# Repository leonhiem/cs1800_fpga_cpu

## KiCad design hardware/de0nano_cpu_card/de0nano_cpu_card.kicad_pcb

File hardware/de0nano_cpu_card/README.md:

# CS1800 DE0-Nano CPU Card (KiCad project)

Eurocard CPU board that plugs a Terasic DE0-Nano (running a VHDL CDP1802 core) into the
existing CS1800 backplane, replacing the original 1802 CPU board.

## Opening this project

Use **KiCad 10.0.6** (`~/bin/kicad-10.0.6-x86_64.AppImage`), not the older KiCad 6 install
that's on `PATH` — this project's files are in KiCad 10's native format and KiCad 6 will
not open them.

```
~/bin/kicad-10.0.6-x86_64.AppImage hardware/de0nano_cpu_card/de0nano_cpu_card.kicad_pro
```

Headless checks (ERC/DRC/export) can be run without launching the GUI via the wrapper
script `~/bin/kicad-cli10` (FUSE-mounts the AppImage's `kicad-cli` on demand, no full
extraction needed):

```
~/bin/kicad-cli10 sch erc de0nano_cpu_card.kicad_sch
~/bin/kicad-cli10 pcb drc de0nano_cpu_card.kicad_pcb
```

## Status (2026-10-09)

Architecture, mechanical/sourcing, and FPGA pin assignment are all resolved. All 7
schematic sheets are wired with real nets (`kicad-cli sch erc`: 0 errors) — see
`docs/design_notes.md` for the full writeup, the JLCPCB-oriented component shortlist,
and the "Next steps" list (custom footprints, PCB floorplan/routing are what's left).
The sheets were generated via the scripts in `tools/` (see `tools/README.md`) from the
pin data in `docs/cs1800.qsf` and the other `docs/` files — re-run the relevant
`tools/build_*.py` after a pinout change rather than hand-editing the `.kicad_sch` output.

## Layout

```
de0nano_cpu_card.kicad_pro/.kicad_sch/.kicad_pcb   top-level project + root (hierarchical) schematic + PCB
sheets/                                             one schematic per functional block
libraries/symbols/cs1800.kicad_sym                  project-local custom symbols
libraries/footprints/cs1800.pretty/                 project-local custom footprints
docs/                                                design notes, pinout docs, FPGA .qsf, connector datasheet
tools/                                               schematic generator scripts (see tools/README.md)
jlcpcb/                                              (empty for now) gerbers/BOM/CPL export target once ready
```

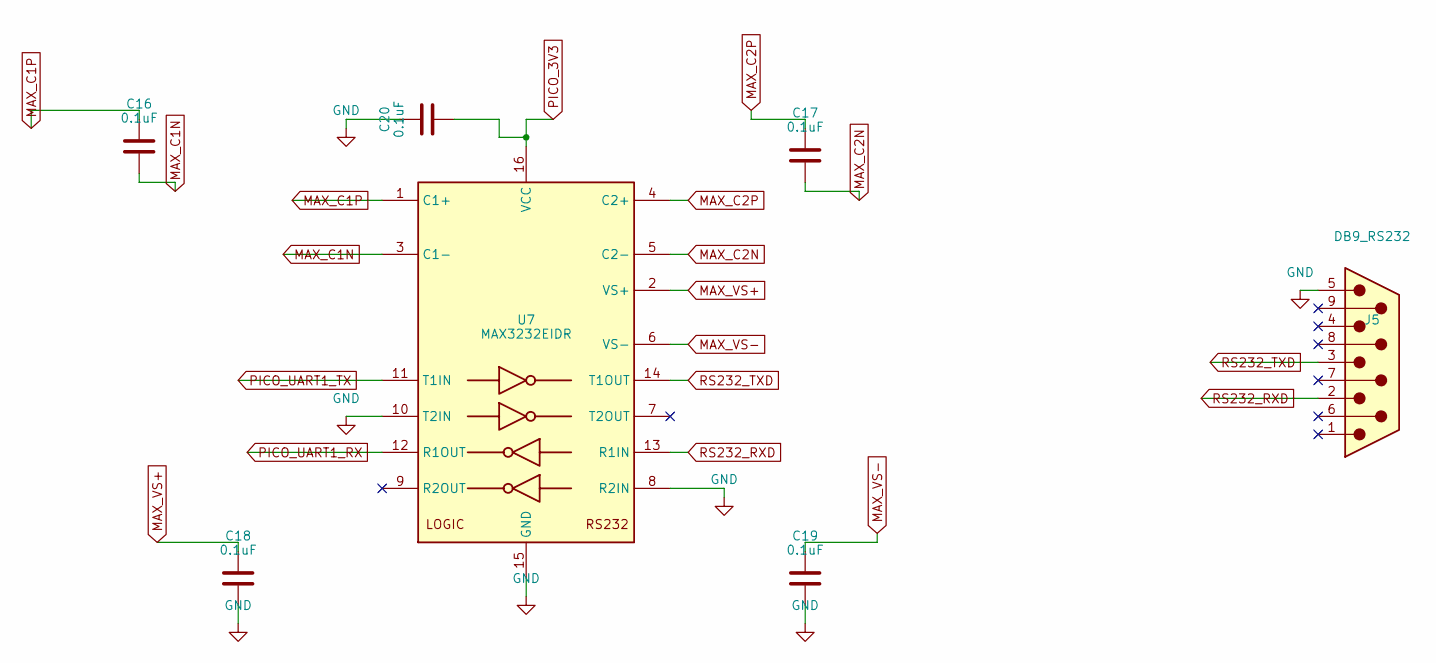
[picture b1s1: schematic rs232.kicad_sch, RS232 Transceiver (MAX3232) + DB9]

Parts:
C16, C17, C18, C19, C20: 0.1uF; C_0603_1608Metric
J5: DB9_RS232; DSUB-9_Pins_Horizontal_P2.77x2.54mm_EdgePinOffset9.40mm
U7: MAX3232EIDR; SOIC-16_3.9x9.9mm_P1.27mm

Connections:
GND: C18.2, C19.2, C20.1, J5.5, U7.8 (R2IN), U7.10 (T2IN), U7.15 (GND); also elsewhere on the board
MAX_C1N: C16.2, U7.3 (C1-)
MAX_C1P: C16.1, U7.1 (C1+)
MAX_C2N: C17.2, U7.5 (C2-)
MAX_C2P: C17.1, U7.4 (C2+)
MAX_VS+: C18.1, U7.2 (VS+)
MAX_VS-: C19.1, U7.6 (VS-)
PICO_3V3: C20.2, U7.16 (VCC); also elsewhere on the board
PICO_UART1_RX: U7.12 (R1OUT); also elsewhere on the board
PICO_UART1_TX: U7.11 (T1IN); also elsewhere on the board
RS232_RXD: J5.2, U7.13 (R1IN)
RS232_TXD: J5.3, U7.14 (T1OUT)

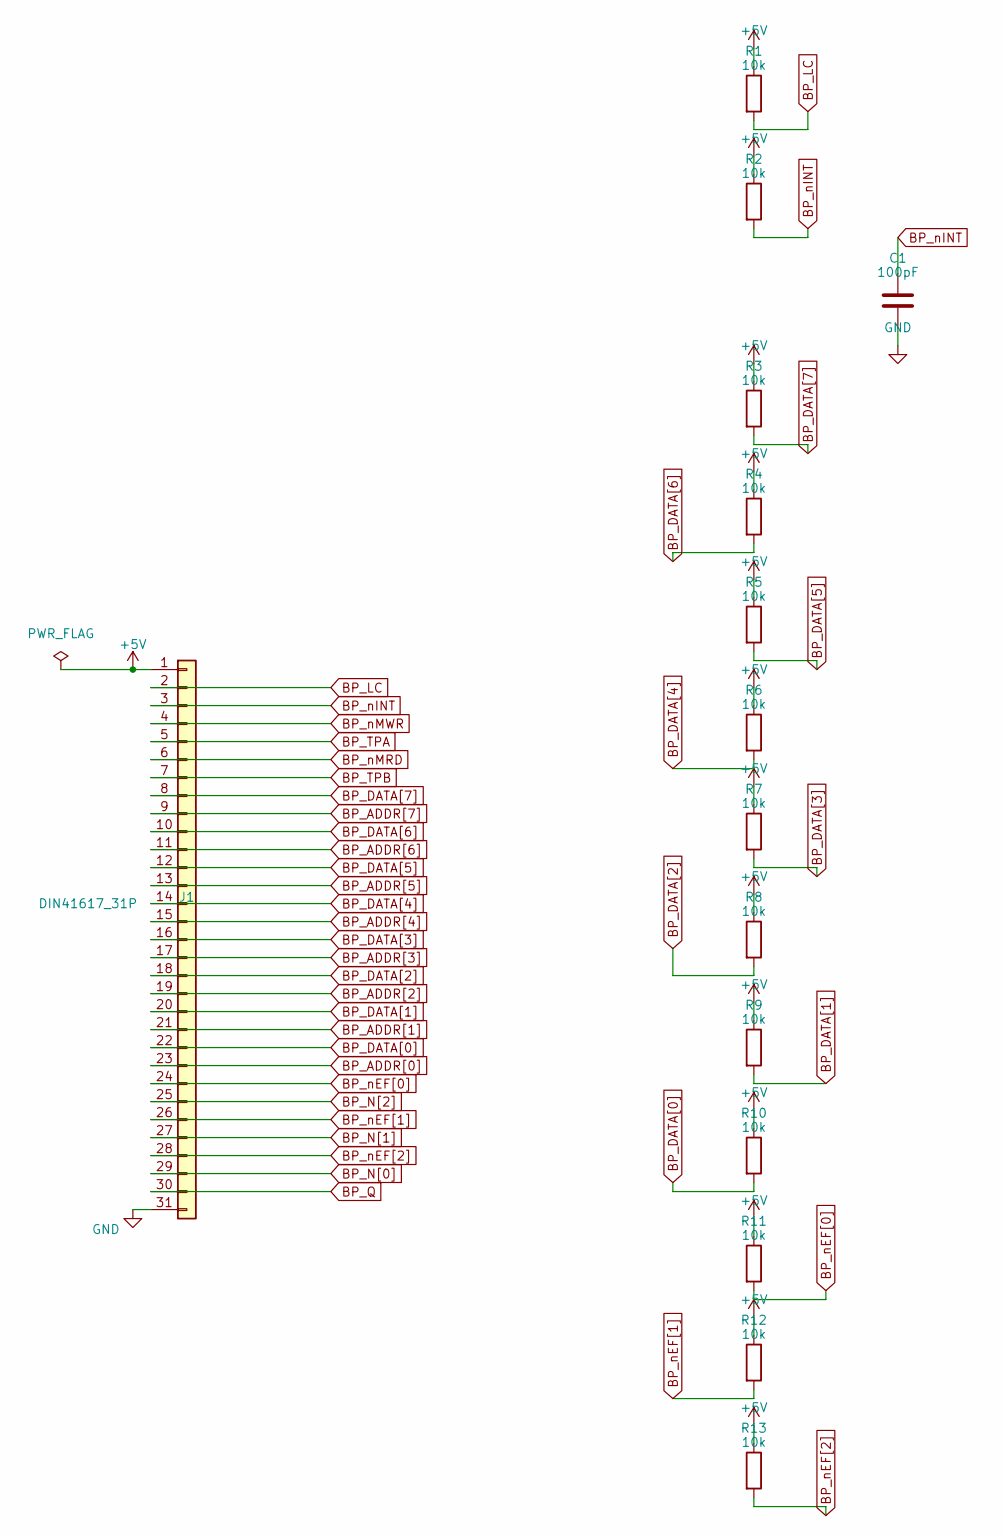
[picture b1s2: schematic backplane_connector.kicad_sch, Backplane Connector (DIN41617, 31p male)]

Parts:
C1: 100pF; C_0603_1608Metric
J1: DIN41617_31P; DIN41617_31P_Male_Angled
R1, R2, R3, R4, R5, R6, R7, R8, R9, R10, R11, R12, R13: 10k; R_0603_1608Metric

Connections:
+5V: J1.1, R1.1, R2.1, R3.1, R4.1, R5.1, R6.1, R7.1, R8.1, R9.1, R10.1, R11.1, R12.1, R13.1; also elsewhere on the board
BP_ADDR[0]: J1.23; also elsewhere on the board
BP_ADDR[1]: J1.21; also elsewhere on the board
BP_ADDR[2]: J1.19; also elsewhere on the board
BP_ADDR[3]: J1.17; also elsewhere on the board
BP_ADDR[4]: J1.15; also elsewhere on the board
BP_ADDR[5]: J1.13; also elsewhere on the board
BP_ADDR[6]: J1.11; also elsewhere on the board
BP_ADDR[7]: J1.9; also elsewhere on the board
BP_DATA[0]: J1.22, R10.2; also elsewhere on the board
BP_DATA[1]: J1.20, R9.2; also elsewhere on the board
BP_DATA[2]: J1.18, R8.2; also elsewhere on the board
BP_DATA[3]: J1.16, R7.2; also elsewhere on the board
BP_DATA[4]: J1.14, R6.2; also elsewhere on the board
BP_DATA[5]: J1.12, R5.2; also elsewhere on the board
BP_DATA[6]: J1.10, R4.2; also elsewhere on the board
BP_DATA[7]: J1.8, R3.2; also elsewhere on the board
BP_LC: J1.2, R1.2; also elsewhere on the board
BP_N[0]: J1.29; also elsewhere on the board
BP_N[1]: J1.27; also elsewhere on the board
BP_N[2]: J1.25; also elsewhere on the board
BP_Q: J1.30; also elsewhere on the board
BP_TPA: J1.5; also elsewhere on the board
BP_TPB: J1.7; also elsewhere on the board
BP_nEF[0]: J1.24, R11.2; also elsewhere on the board
BP_nEF[1]: J1.26, R12.2; also elsewhere on the board
BP_nEF[2]: J1.28, R13.2; also elsewhere on the board
BP_nINT: C1.1, J1.3, R2.2; also elsewhere on the board
BP_nMRD: J1.6; also elsewhere on the board
BP_nMWR: J1.4; also elsewhere on the board
GND: C1.2, J1.31; also elsewhere on the board

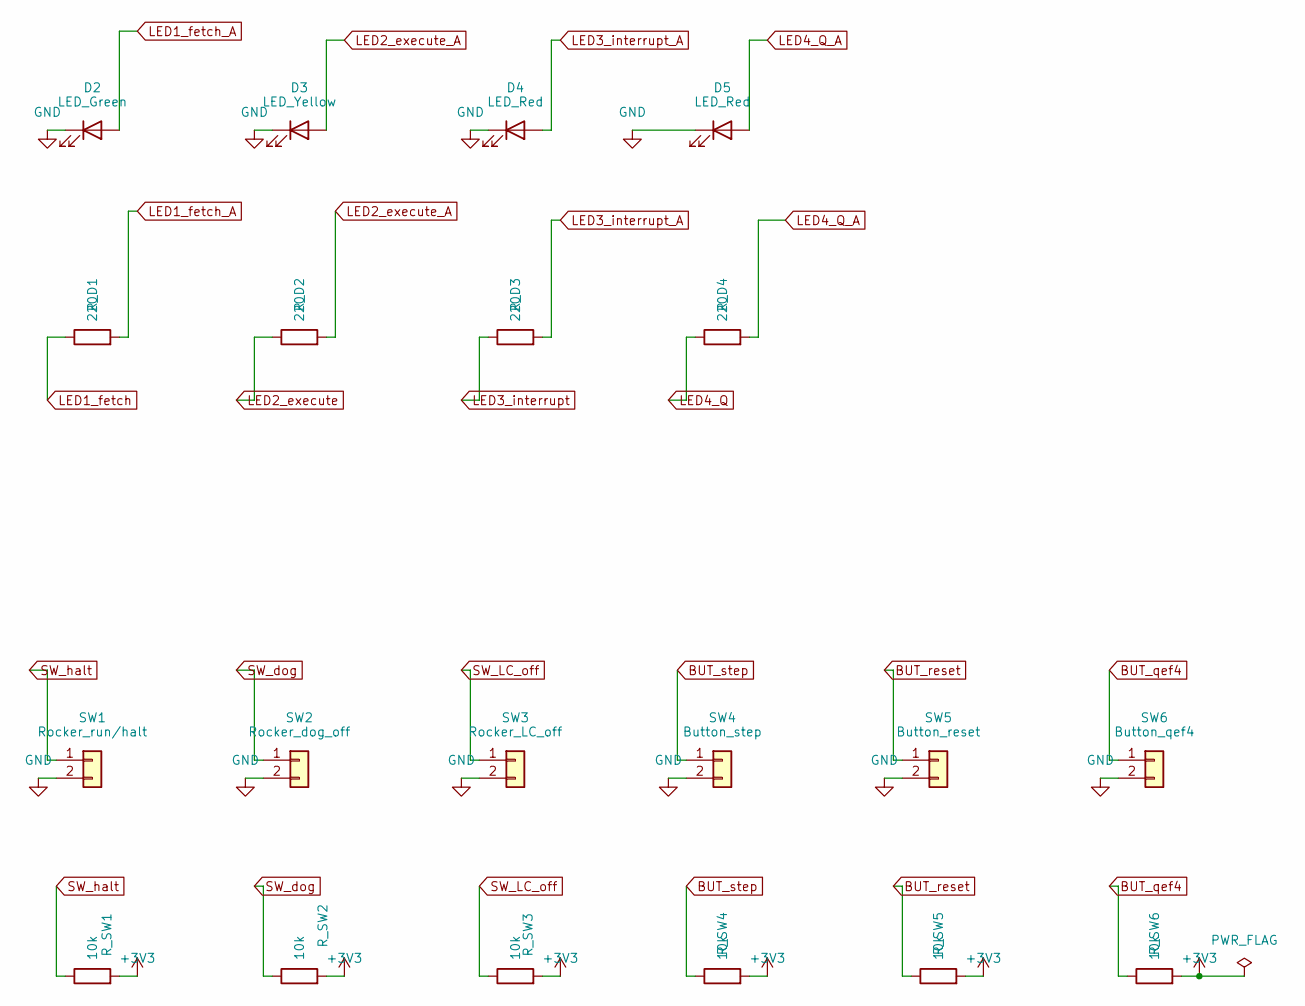
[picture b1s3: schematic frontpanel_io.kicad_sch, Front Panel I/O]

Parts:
D2: LED_Green; LED_D3.0mm
D3: LED_Yellow; LED_D3.0mm
D4, D5: LED_Red; LED_D3.0mm
R_D1, R_D2, R_D3, R_D4: 220; R_0603_1608Metric
R_SW1, R_SW2, R_SW3, R_SW4, R_SW5, R_SW6: 10k; R_0603_1608Metric
SW1: Rocker_run/halt; PinHeader_1x02_P2.54mm_Vertical
SW2: Rocker_dog_off; PinHeader_1x02_P2.54mm_Vertical
SW3: Rocker_LC_off; PinHeader_1x02_P2.54mm_Vertical
SW4: Button_step; PinHeader_1x02_P2.54mm_Vertical
SW5: Button_reset; PinHeader_1x02_P2.54mm_Vertical
SW6: Button_qef4; PinHeader_1x02_P2.54mm_Vertical

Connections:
+3V3: R_SW1.2, R_SW2.2, R_SW3.2, R_SW4.2, R_SW5.2, R_SW6.2; also elsewhere on the board
BUT_qef4: R_SW6.1, SW6.1; also elsewhere on the board
BUT_reset: R_SW5.1, SW5.1; also elsewhere on the board
BUT_step: R_SW4.1, SW4.1; also elsewhere on the board
GND: D2.1 (K), D3.1 (K), D4.1 (K), D5.1 (K), SW1.2, SW2.2, SW3.2, SW4.2, SW5.2, SW6.2; also elsewhere on the board
LED1_fetch: R_D1.1; also elsewhere on the board
LED1_fetch_A: D2.2 (A), R_D1.2
LED2_execute: R_D2.1; also elsewhere on the board
LED2_execute_A: D3.2 (A), R_D2.2
LED3_interrupt: R_D3.1; also elsewhere on the board
LED3_interrupt_A: D4.2 (A), R_D3.2
LED4_Q: R_D4.1; also elsewhere on the board
LED4_Q_A: D5.2 (A), R_D4.2
SW_LC_off: R_SW3.1, SW3.1; also elsewhere on the board
SW_dog: R_SW2.1, SW2.1; also elsewhere on the board
SW_halt: R_SW1.1, SW1.1; also elsewhere on the board

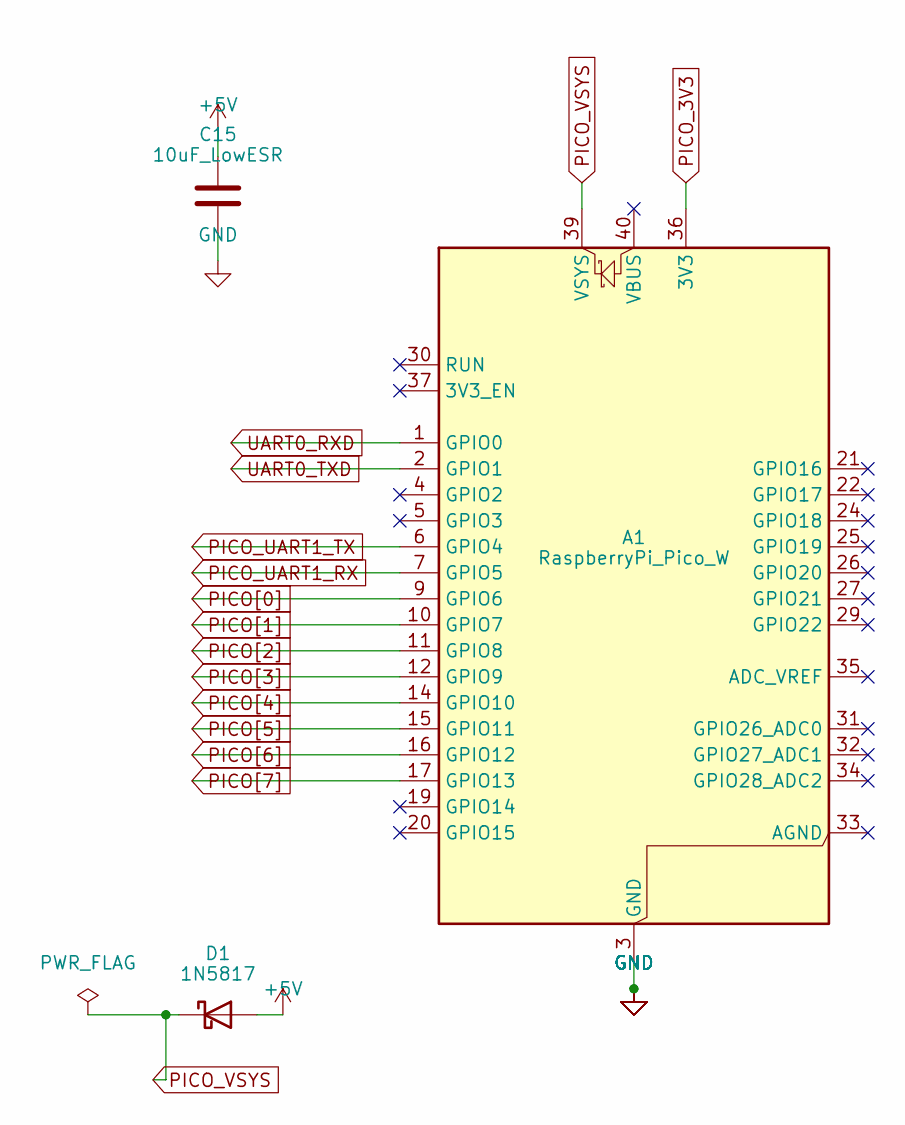
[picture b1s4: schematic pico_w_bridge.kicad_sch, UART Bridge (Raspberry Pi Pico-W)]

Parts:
A1: RaspberryPi_Pico_W; RaspberryPi_Pico_W_SocketHeaders_2x1x20_P2.54mm
C15: 10uF_LowESR; C_1210_3225Metric
D1: 1N5817; D_SMA

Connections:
+5V: C15.1, D1.2 (A); also elsewhere on the board
GND: A1.3 (GND), A1.8 (GND), A1.13 (GND), A1.18 (GND), A1.23 (GND), A1.28 (GND), A1.38 (GND), C15.2; also elsewhere on the board
PICO[0]: A1.9 (GPIO6); also elsewhere on the board
PICO[1]: A1.10 (GPIO7); also elsewhere on the board
PICO[2]: A1.11 (GPIO8); also elsewhere on the board
PICO[3]: A1.12 (GPIO9); also elsewhere on the board
PICO[4]: A1.14 (GPIO10); also elsewhere on the board
PICO[5]: A1.15 (GPIO11); also elsewhere on the board
PICO[6]: A1.16 (GPIO12); also elsewhere on the board
PICO[7]: A1.17 (GPIO13); also elsewhere on the board
PICO_3V3: A1.36 (3V3); also elsewhere on the board
PICO_UART1_RX: A1.7 (GPIO5); also elsewhere on the board
PICO_UART1_TX: A1.6 (GPIO4); also elsewhere on the board
PICO_VSYS: A1.39 (VSYS), D1.1 (K)
UART0_RXD: A1.1 (GPIO0); also elsewhere on the board
UART0_TXD: A1.2 (GPIO1); also elsewhere on the board

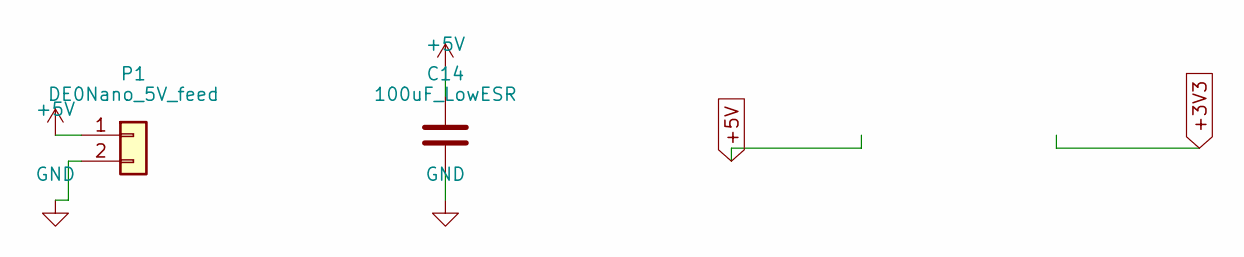
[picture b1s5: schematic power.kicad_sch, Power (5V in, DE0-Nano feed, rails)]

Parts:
C14: 100uF_LowESR; C_1210_3225Metric
P1: DE0Nano_5V_feed; PinHeader_1x02_P2.54mm_Vertical

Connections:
+5V: C14.1, P1.1; also elsewhere on the board
GND: C14.2, P1.2; also elsewhere on the board

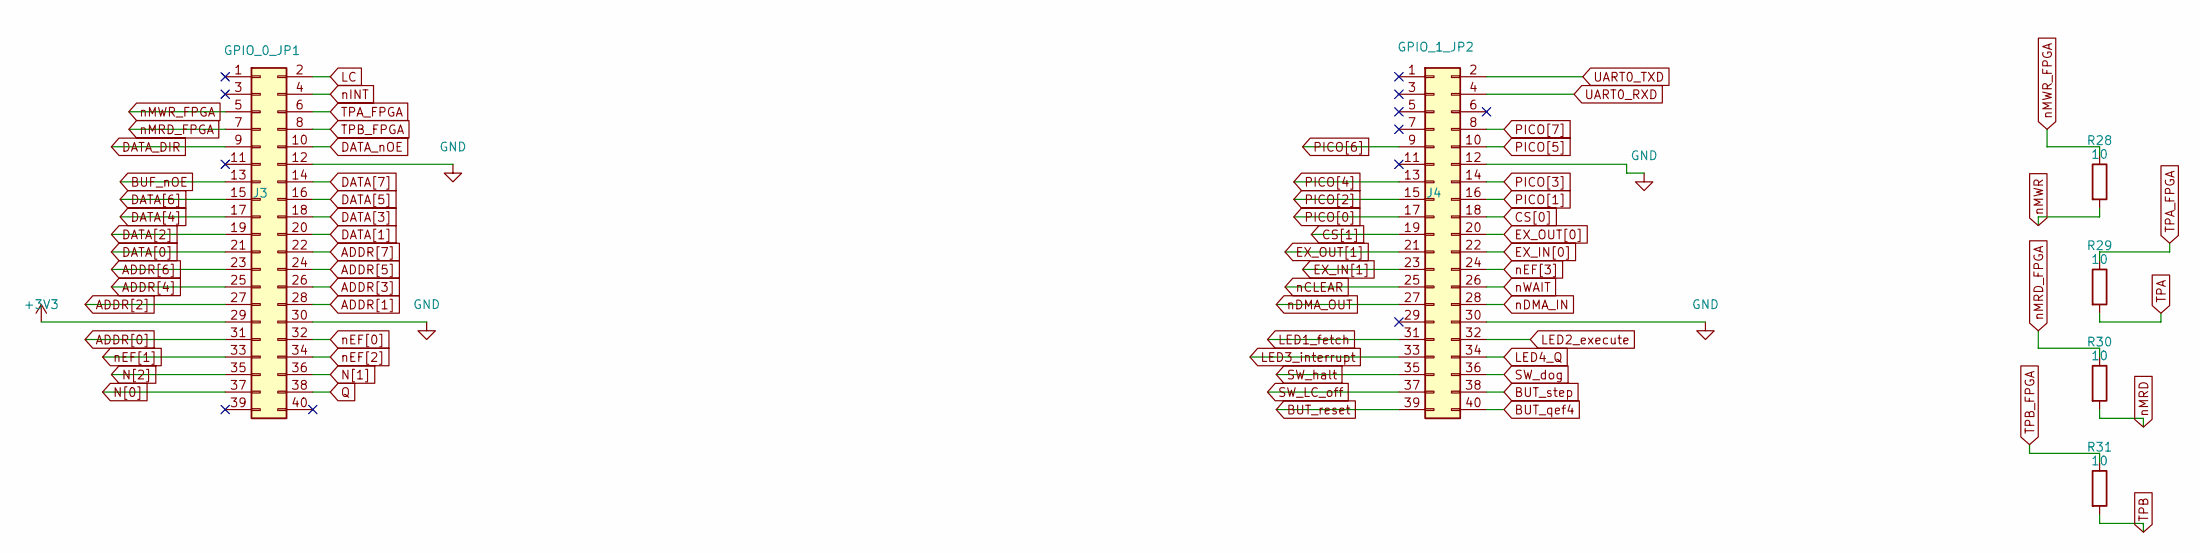
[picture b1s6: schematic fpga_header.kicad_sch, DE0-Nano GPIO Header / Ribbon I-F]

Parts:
J3: GPIO_0_JP1; IDC-Header_2x20_P2.54mm_Vertical
J4: GPIO_1_JP2; IDC-Header_2x20_P2.54mm_Vertical
R28, R29, R30, R31: 10; R_0603_1608Metric

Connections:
+3V3: J3.29; also elsewhere on the board
ADDR[0]: J3.31; also elsewhere on the board
ADDR[1]: J3.28; also elsewhere on the board
ADDR[2]: J3.27; also elsewhere on the board
ADDR[3]: J3.26; also elsewhere on the board
ADDR[4]: J3.25; also elsewhere on the board
ADDR[5]: J3.24; also elsewhere on the board
ADDR[6]: J3.23; also elsewhere on the board
ADDR[7]: J3.22; also elsewhere on the board
BUF_nOE: J3.13; also elsewhere on the board
BUT_qef4: J4.40; also elsewhere on the board
BUT_reset: J4.39; also elsewhere on the board
BUT_step: J4.38; also elsewhere on the board
CS[0]: J4.18; also elsewhere on the board
CS[1]: J4.19; also elsewhere on the board
DATA[0]: J3.21; also elsewhere on the board
DATA[1]: J3.20; also elsewhere on the board
DATA[2]: J3.19; also elsewhere on the board
DATA[3]: J3.18; also elsewhere on the board
DATA[4]: J3.17; also elsewhere on the board
DATA[5]: J3.16; also elsewhere on the board
DATA[6]: J3.15; also elsewhere on the board
DATA[7]: J3.14; also elsewhere on the board
DATA_DIR: J3.9; also elsewhere on the board
DATA_nOE: J3.10; also elsewhere on the board
EX_IN[0]: J4.22; also elsewhere on the board
EX_IN[1]: J4.23; also elsewhere on the board
EX_OUT[0]: J4.20; also elsewhere on the board
EX_OUT[1]: J4.21; also elsewhere on the board
GND: J3.12, J3.30, J4.12, J4.30; also elsewhere on the board
LC: J3.2; also elsewhere on the board
LED1_fetch: J4.31; also elsewhere on the board
LED2_execute: J4.32; also elsewhere on the board
LED3_interrupt: J4.33; also elsewhere on the board
LED4_Q: J4.34; also elsewhere on the board
N[0]: J3.37; also elsewhere on the board
N[1]: J3.36; also elsewhere on the board
N[2]: J3.35; also elsewhere on the board
PICO[0]: J4.17; also elsewhere on the board
PICO[1]: J4.16; also elsewhere on the board
PICO[2]: J4.15; also elsewhere on the board
PICO[3]: J4.14; also elsewhere on the board
PICO[4]: J4.13; also elsewhere on the board
PICO[5]: J4.10; also elsewhere on the board
PICO[6]: J4.9; also elsewhere on the board
PICO[7]: J4.8; also elsewhere on the board
Q: J3.38; also elsewhere on the board
SW_LC_off: J4.37; also elsewhere on the board
SW_dog: J4.36; also elsewhere on the board
SW_halt: J4.35; also elsewhere on the board
TPA: R29.2; also elsewhere on the board
TPA_FPGA: J3.6, R29.1
TPB: R31.2; also elsewhere on the board
TPB_FPGA: J3.8, R31.1
UART0_RXD: J4.4; also elsewhere on the board
UART0_TXD: J4.2; also elsewhere on the board
nCLEAR: J4.25; also elsewhere on the board
nDMA_IN: J4.28; also elsewhere on the board
nDMA_OUT: J4.27; also elsewhere on the board
nEF[0]: J3.32; also elsewhere on the board
nEF[1]: J3.33; also elsewhere on the board
nEF[2]: J3.34; also elsewhere on the board
nEF[3]: J4.24; also elsewhere on the board
nINT: J3.4; also elsewhere on the board
nMRD: R30.2; also elsewhere on the board
nMRD_FPGA: J3.7, R30.1
nMWR: R28.2; also elsewhere on the board
nMWR_FPGA: J3.5, R28.1
nWAIT: J4.26; also elsewhere on the board

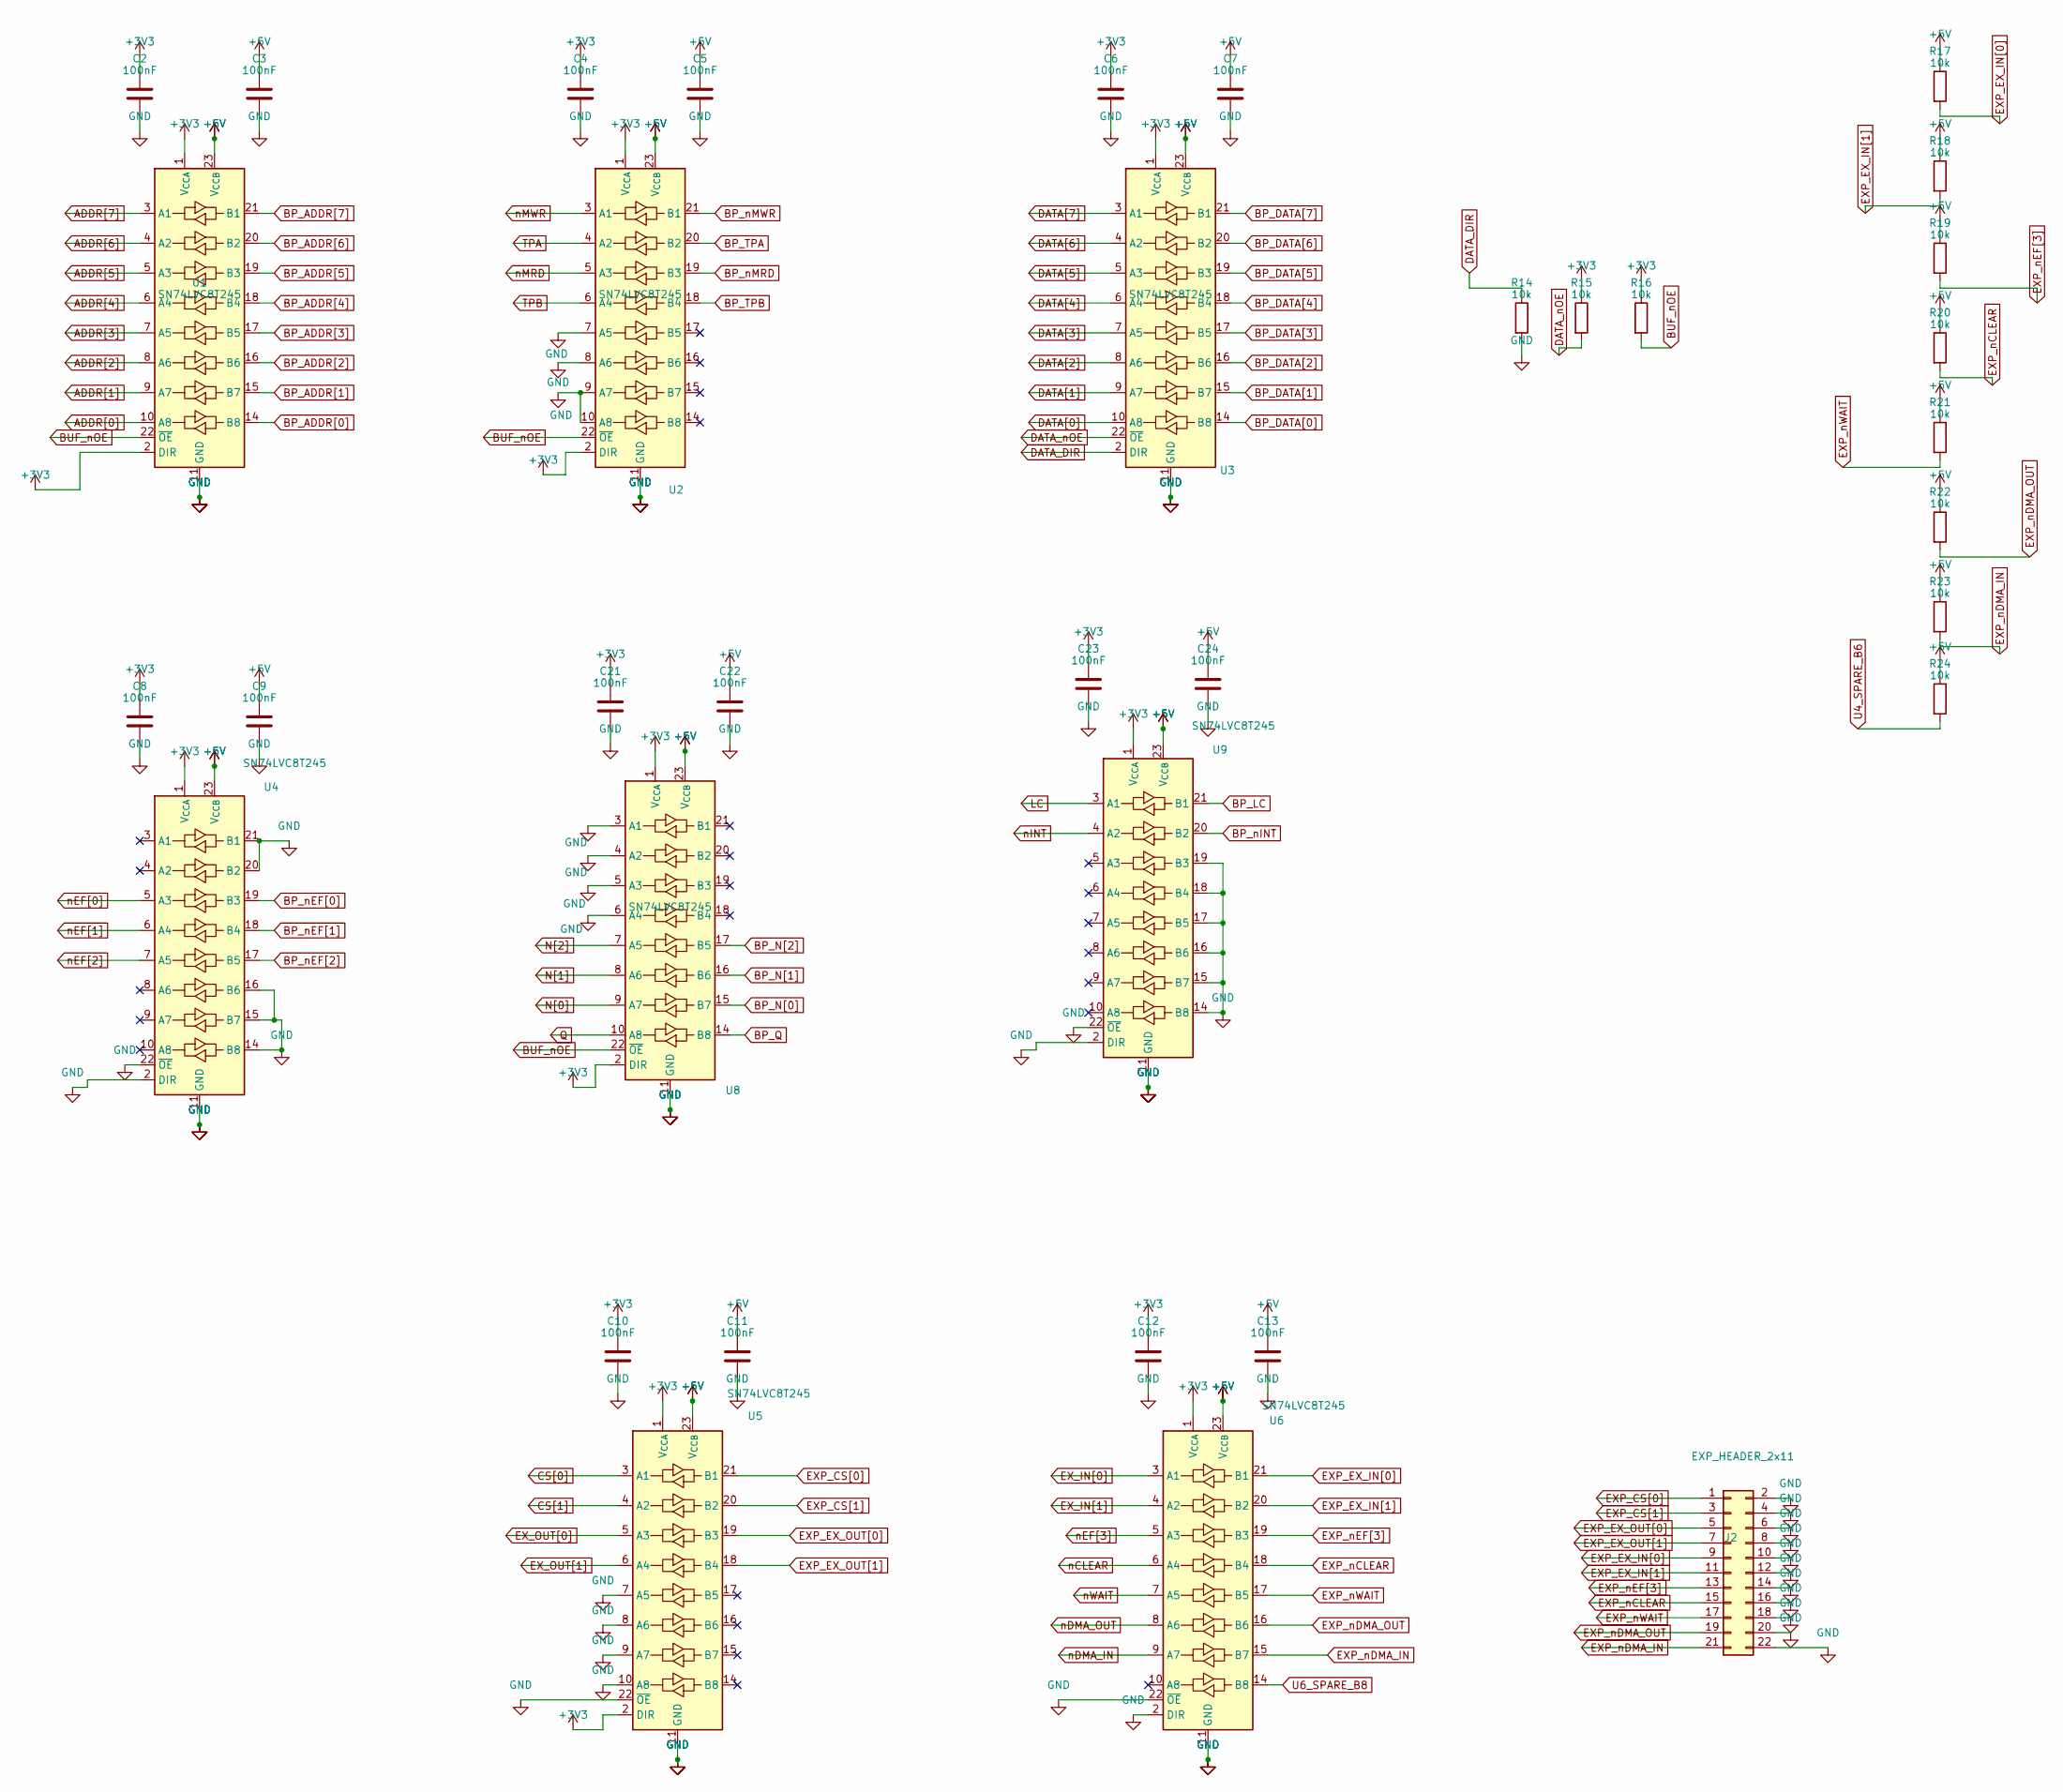
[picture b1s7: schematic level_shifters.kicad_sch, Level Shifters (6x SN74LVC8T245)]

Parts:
C2, C3, C4, C5, C6, C7, C8, C9, C10, C11, C12, C13, C21, C22, C23, C24: 100nF; C_0603_1608Metric
J2: EXP_HEADER_2x11; PinHeader_2x11_P2.54mm_Vertical
R14, R15, R16, R17, R18, R19, R20, R21, R22, R23, R24: 10k; R_0603_1608Metric
U1, U2, U3, U4, U5, U6, U8, U9: SN74LVC8T245; TSSOP-24_4.4x7.8mm_P0.65mm

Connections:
+3V3: C2.1, C4.1, C6.1, C8.1, C10.1, C12.1, C21.1, C23.1, R15.1, R16.1, U1.1 (V_{CCA}), U1.2 (DIR), U2.1 (V_{CCA}), U2.2 (DIR), U3.1 (V_{CCA}), U4.1 (V_{CCA}), U5.1 (V_{CCA}), U5.2 (DIR), U6.1 (V_{CCA}), U8.1 (V_{CCA}), U8.2 (DIR), U9.1 (V_{CCA}); also elsewhere on the board
+5V: C3.1, C5.1, C7.1, C9.1, C11.1, C13.1, C22.1, C24.1, R17.1, R18.1, R19.1, R20.1, R21.1, R22.1, R23.1, R24.1, U1.23 (V_{CCB}), U1.24 (V_{CCB}), U2.23 (V_{CCB}), U2.24 (V_{CCB}), U3.23 (V_{CCB}), U3.24 (V_{CCB}), U4.23 (V_{CCB}), U4.24 (V_{CCB}), U5.23 (V_{CCB}), U5.24 (V_{CCB}), U6.23 (V_{CCB}), U6.24 (V_{CCB}), U8.23 (V_{CCB}), U8.24 (V_{CCB}), U9.23 (V_{CCB}), U9.24 (V_{CCB}); also elsewhere on the board
ADDR[0]: U1.10 (A8); also elsewhere on the board
ADDR[1]: U1.9 (A7); also elsewhere on the board
ADDR[2]: U1.8 (A6); also elsewhere on the board
ADDR[3]: U1.7 (A5); also elsewhere on the board
ADDR[4]: U1.6 (A4); also elsewhere on the board
ADDR[5]: U1.5 (A3); also elsewhere on the board
ADDR[6]: U1.4 (A2); also elsewhere on the board
ADDR[7]: U1.3 (A1); also elsewhere on the board
BP_ADDR[0]: U1.14 (B8); also elsewhere on the board
BP_ADDR[1]: U1.15 (B7); also elsewhere on the board
BP_ADDR[2]: U1.16 (B6); also elsewhere on the board
BP_ADDR[3]: U1.17 (B5); also elsewhere on the board
BP_ADDR[4]: U1.18 (B4); also elsewhere on the board
BP_ADDR[5]: U1.19 (B3); also elsewhere on the board
BP_ADDR[6]: U1.20 (B2); also elsewhere on the board
BP_ADDR[7]: U1.21 (B1); also elsewhere on the board
BP_DATA[0]: U3.14 (B8); also elsewhere on the board
BP_DATA[1]: U3.15 (B7); also elsewhere on the board
BP_DATA[2]: U3.16 (B6); also elsewhere on the board
BP_DATA[3]: U3.17 (B5); also elsewhere on the board
BP_DATA[4]: U3.18 (B4); also elsewhere on the board
BP_DATA[5]: U3.19 (B3); also elsewhere on the board
BP_DATA[6]: U3.20 (B2); also elsewhere on the board
BP_DATA[7]: U3.21 (B1); also elsewhere on the board
BP_LC: U9.21 (B1); also elsewhere on the board
BP_N[0]: U8.15 (B7); also elsewhere on the board
BP_N[1]: U8.16 (B6); also elsewhere on the board
BP_N[2]: U8.17 (B5); also elsewhere on the board
BP_Q: U8.14 (B8); also elsewhere on the board
BP_TPA: U2.20 (B2); also elsewhere on the board
BP_TPB: U2.18 (B4); also elsewhere on the board
BP_nEF[0]: U4.19 (B3); also elsewhere on the board
BP_nEF[1]: U4.18 (B4); also elsewhere on the board
BP_nEF[2]: U4.17 (B5); also elsewhere on the board
BP_nINT: U9.20 (B2); also elsewhere on the board
BP_nMRD: U2.19 (B3); also elsewhere on the board
BP_nMWR: U2.21 (B1); also elsewhere on the board
BUF_nOE: R16.2, U1.22 (~OE), U2.22 (~OE), U8.22 (~OE); also elsewhere on the board
CS[0]: U5.3 (A1); also elsewhere on the board
CS[1]: U5.4 (A2); also elsewhere on the board
DATA[0]: U3.10 (A8); also elsewhere on the board
DATA[1]: U3.9 (A7); also elsewhere on the board
DATA[2]: U3.8 (A6); also elsewhere on the board
DATA[3]: U3.7 (A5); also elsewhere on the board
DATA[4]: U3.6 (A4); also elsewhere on the board
DATA[5]: U3.5 (A3); also elsewhere on the board
DATA[6]: U3.4 (A2); also elsewhere on the board
DATA[7]: U3.3 (A1); also elsewhere on the board
DATA_DIR: R14.1, U3.2 (DIR); also elsewhere on the board
DATA_nOE: R15.2, U3.22 (~OE); also elsewhere on the board
EXP_CS[0]: J2.1, U5.21 (B1)
EXP_CS[1]: J2.3, U5.20 (B2)
EXP_EX_IN[0]: J2.9, R17.2, U6.21 (B1)
EXP_EX_IN[1]: J2.11, R18.2, U6.20 (B2)
EXP_EX_OUT[0]: J2.5, U5.19 (B3)
EXP_EX_OUT[1]: J2.7, U5.18 (B4)
EXP_nCLEAR: J2.15, R20.2, U6.18 (B4)
EXP_nDMA_IN: J2.21, R23.2, U6.15 (B7)
EXP_nDMA_OUT: J2.19, R22.2, U6.16 (B6)
EXP_nEF[3]: J2.13, R19.2, U6.19 (B3)
EXP_nWAIT: J2.17, R21.2, U6.17 (B5)
EX_IN[0]: U6.3 (A1); also elsewhere on the board
EX_IN[1]: U6.4 (A2); also elsewhere on the board
EX_OUT[0]: U5.5 (A3); also elsewhere on the board
EX_OUT[1]: U5.6 (A4); also elsewhere on the board
GND: C2.2, C3.2, C4.2, C5.2, C6.2, C7.2, C8.2, C9.2, C10.2, C11.2, C12.2, C13.2, C21.2, C22.2, C23.2, C24.2, J2.2, J2.4, J2.6, J2.8, J2.10, J2.12, J2.14, J2.16, J2.18, J2.20, J2.22, R14.2, U1.11 (GND), U1.12 (GND), U1.13 (GND), U2.7 (A5), U2.8 (A6), U2.9 (A7), U2.10 (A8), U2.11 (GND), U2.12 (GND), U2.13 (GND), U3.11 (GND), U3.12 (GND), U3.13 (GND), U4.2 (DIR), U4.11 (GND), U4.12 (GND), U4.13 (GND), U4.14 (B8), U4.15 (B7), U4.16 (B6), U4.20 (B2), U4.21 (B1), U4.22 (~OE), U5.7 (A5), U5.8 (A6), U5.9 (A7), U5.10 (A8), U5.11 (GND), U5.12 (GND), U5.13 (GND), U5.22 (~OE), U6.2 (DIR), U6.11 (GND), U6.12 (GND), U6.13 (GND), U6.22 (~OE), U8.3 (A1), U8.4 (A2), U8.5 (A3), U8.6 (A4), U8.11 (GND), U8.12 (GND), U8.13 (GND), U9.2 (DIR), U9.11 (GND), U9.12 (GND), U9.13 (GND), U9.14 (B8), U9.15 (B7), U9.16 (B6), U9.17 (B5), U9.18 (B4), U9.19 (B3), U9.22 (~OE); also elsewhere on the board
LC: U9.3 (A1); also elsewhere on the board
N[0]: U8.9 (A7); also elsewhere on the board
N[1]: U8.8 (A6); also elsewhere on the board
N[2]: U8.7 (A5); also elsewhere on the board
Q: U8.10 (A8); also elsewhere on the board
TPA: U2.4 (A2); also elsewhere on the board
TPB: U2.6 (A4); also elsewhere on the board
nCLEAR: U6.6 (A4); also elsewhere on the board
nDMA_IN: U6.9 (A7); also elsewhere on the board
nDMA_OUT: U6.8 (A6); also elsewhere on the board
nEF[0]: U4.5 (A3); also elsewhere on the board
nEF[1]: U4.6 (A4); also elsewhere on the board
nEF[2]: U4.7 (A5); also elsewhere on the board
nEF[3]: U6.5 (A3); also elsewhere on the board
nINT: U9.4 (A2); also elsewhere on the board
nMRD: U2.5 (A3); also elsewhere on the board
nMWR: U2.3 (A1); also elsewhere on the board
nWAIT: U6.7 (A5); also elsewhere on the board

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
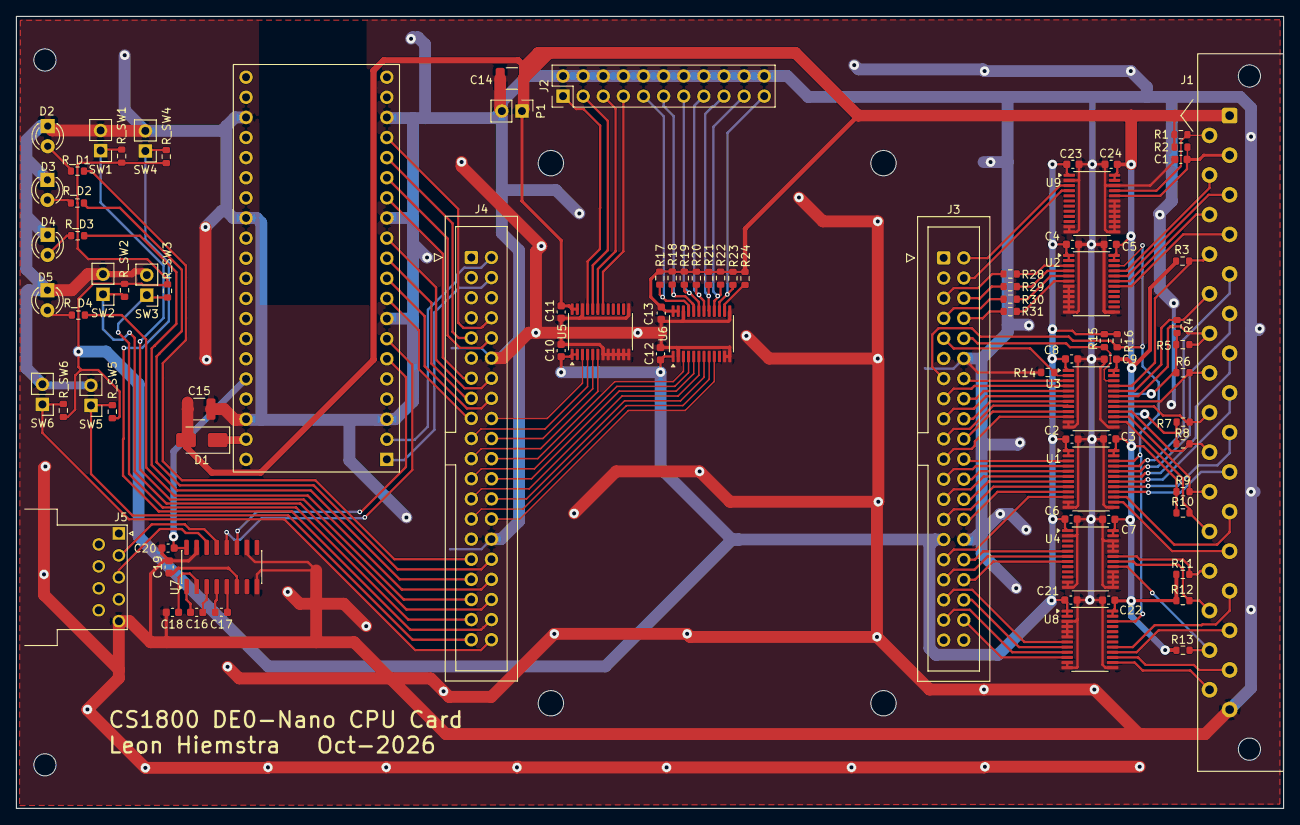
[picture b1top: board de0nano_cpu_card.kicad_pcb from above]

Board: 2 copper layers, 160.0 x 100.0 mm, 92 parts (0 on the bottom side), 127 nets.

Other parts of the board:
DE0NANO: DE0-Nano (reference); DE0Nano_Reference_Outline
MH1, MH2: f; MountingHole_2.8mm

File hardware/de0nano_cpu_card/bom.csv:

"Designator","Comment","Footprint","Qty","DNP"
"A1","RaspberryPi_Pico_W","cs1800:RaspberryPi_Pico_W_SocketHeaders_2x1x20_P2.54mm","1",""
"C1","100pF","Capacitor_SMD:C_0603_1608Metric","1",""
"C2,C3,C4,C5,C6,C7,C8,C9,C10,C11,C12,C13,C21,C22,C23,C24","100nF","Capacitor_SMD:C_0603_1608Metric","16",""
"C14","100uF_LowESR","Capacitor_SMD:C_1210_3225Metric","1",""
"C15","10uF_LowESR","Capacitor_SMD:C_1210_3225Metric","1",""
"C16,C17,C18,C19,C20","0.1uF","Capacitor_SMD:C_0603_1608Metric","5",""
"D1","1N5817","Diode_SMD:D_SMA","1",""
"D2","LED_Green","LED_THT:LED_D3.0mm","1",""
"D3","LED_Yellow","LED_THT:LED_D3.0mm","1",""
"D4,D5","LED_Red","LED_THT:LED_D3.0mm","2",""
"J1","DIN41617_31P","cs1800:DIN41617_31P_Male_Angled","1",""
"J2","EXP_HEADER_2x11","Connector_PinHeader_2.54mm:PinHeader_2x11_P2.54mm_Vertical","1",""
"J3","GPIO_0_JP1","Connector_IDC:IDC-Header_2x20_P2.54mm_Vertical","1",""
"J4","GPIO_1_JP2","Connector_IDC:IDC-Header_2x20_P2.54mm_Vertical","1",""
"J5","DB9_RS232","Connector_Dsub:DSUB-9_Pins_Horizontal_P2.77x2.54mm_EdgePinOffset9.40mm","1",""
"P1","DE0Nano_5V_feed","Connector_PinHeader_2.54mm:PinHeader_1x02_P2.54mm_Vertical","1",""
"R1,R2,R3,R4,R5,R6,R7,R8,R9,R10,R11,R12,R13,R14,R15,R16,R17,R18,R19,R20,R21,R22,R23,R24,R_SW1,R_SW2,R_SW3,R_SW4,R_SW5,R_SW6","10k","Resistor_SMD:R_0603_1608Metric","30",""
"R28,R29,R30,R31","10","Resistor_SMD:R_0603_1608Metric","4",""
"R_D1,R_D2,R_D3,R_D4","220","Resistor_SMD:R_0603_1608Metric","4",""
"SW1","Rocker_run/halt","Connector_PinHeader_2.54mm:PinHeader_1x02_P2.54mm_Vertical","1",""
"SW2","Rocker_dog_off","Connector_PinHeader_2.54mm:PinHeader_1x02_P2.54mm_Vertical","1",""
"SW3","Rocker_LC_off","Connector_PinHeader_2.54mm:PinHeader_1x02_P2.54mm_Vertical","1",""
"SW4","Button_step","Connector_PinHeader_2.54mm:PinHeader_1x02_P2.54mm_Vertical","1",""
"SW5","Button_reset","Connector_PinHeader_2.54mm:PinHeader_1x02_P2.54mm_Vertical","1",""
"SW6","Button_qef4","Connector_PinHeader_2.54mm:PinHeader_1x02_P2.54mm_Vertical","1",""
"U1,U2,U3,U4,U5,U6,U8,U9","SN74LVC8T245","Package_SO:TSSOP-24_4.4x7.8mm_P0.65mm","8",""
"U7","MAX3232EIDR","Package_SO:SOIC-16_3.9x9.9mm_P1.27mm","1",""
